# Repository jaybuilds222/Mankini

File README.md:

A custom mechanical keyboard design based on FlatFootFox's take on a single-board version of Brian Low's Sofle Choc keyboard, which is itself a redesigned version of the Sofle keyboard by Josef Adamčík. It uses MrZealot's excellent Ergogen engine to layout the design.

I've made two versions so far. One is designed to use Kailh V1 Choc low-profile keyswitches. The other is designed for Cherry MX switches.

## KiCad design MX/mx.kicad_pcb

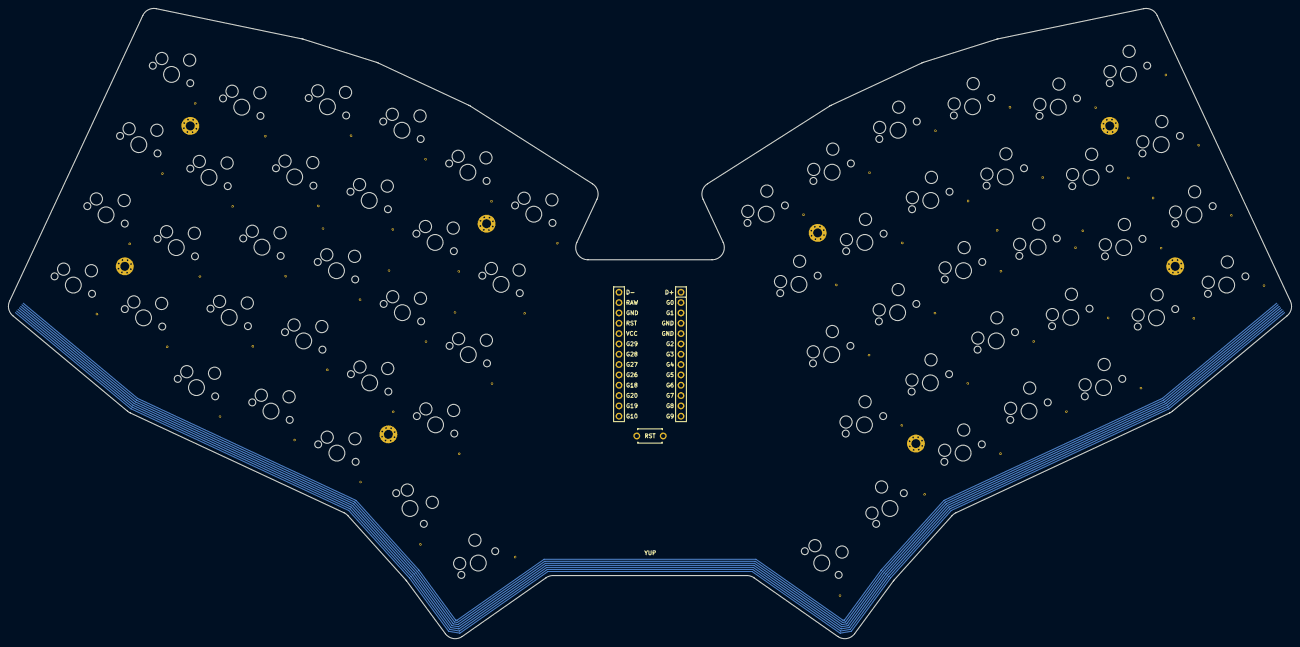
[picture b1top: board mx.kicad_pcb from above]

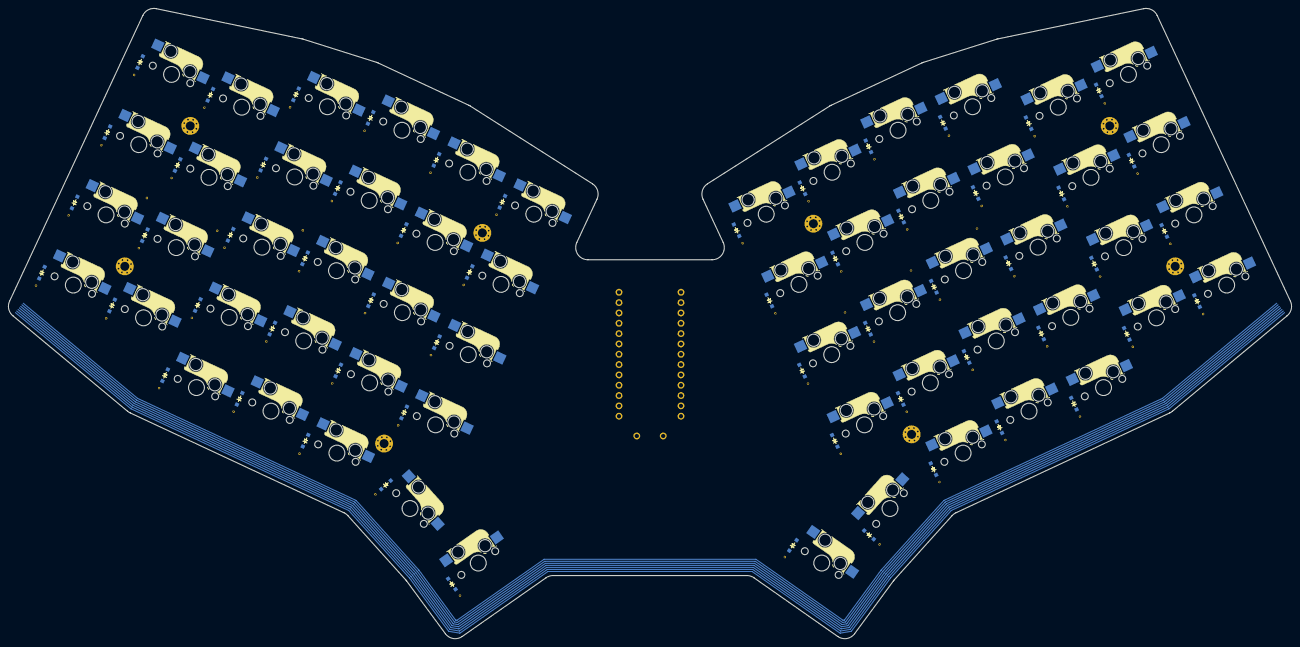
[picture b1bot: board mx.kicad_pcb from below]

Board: 2 copper layers, 315.5 x 155.0 mm, 126 parts (116 on the bottom side), 76 nets, no tracks yet.

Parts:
D1, D2, D3, D4, D5, D6, D7, D8, D9, D10, D11, D12, D13, D14, D15, D16, D17, D18, D19, D20, D21, D22, D23, D24, D25, D26, D27, D28, D29, D30, D31, D32, D33, D34, D35, D36, D37, D38, D39, D40, D41, D42, D43, D44, D45, D46, D47, D48, D49, D50, D51, D52, D53, D54, D55, D56, D57, D58: diode_tht_sod123
MCU1: mcu_rp2040
RST1: reset_switch_tht_top
S1, S2, S3, S4, S5, S6, S7, S8, S9, S10, S11, S12, S13, S14, S15, S16, S17, S18, S19, S20, S21, S22, S23, S24, S25, S26, S27, S28, S29, S30, S31, S32, S33, S34, S35, S36, S37, S38, S39, S40, S41, S42, S43, S44, S45, S46, S47, S48, S49, S50, S51, S52, S53, S54, S55, S56, S57, S58: switch_mx
_65, _66, _67, _68, _69, _70, _71, _72: MountingHole_2.2mm_M2_Pad_Via

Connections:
G2: D33.1, D37.1, D42.1, D47.1, D52.1, D56.1, MCU1.6
G3: D32.1, D36.1, D41.1, D46.1, D51.1, D55.1, MCU1.7
G4: MCU1.8, S1.1, S2.1, S3.1, S4.1, S30.1, S31.1, S32.1, S33.1
G5: MCU1.9, S5.1, S6.1, S7.1, S8.1, S9.1, S34.1, S35.1, S36.1, S37.1, S38.1
G6: MCU1.10, S10.1, S11.1, S12.1, S13.1, S14.1, S39.1, S40.1, S41.1, S42.1, S43.1
G7: D31.1, D35.1, D40.1, D45.1, D50.1, D54.1, MCU1.11
G8: D30.1, D34.1, D39.1, D44.1, D49.1, D53.1, MCU1.12
G9: D38.1, D43.1, D48.1, D57.1, D58.1, MCU1.13
G10: D9.1, D14.1, D19.1, D28.1, D29.1, MCU1.14
G18: MCU1.17, S24.1, S25.1, S26.1, S27.1, S29.1, S53.1, S54.1, S55.1, S56.1, S58.1
G19: D1.1, D5.1, D10.1, D15.1, D20.1, D24.1, MCU1.15
G20: D2.1, D6.1, D11.1, D16.1, D21.1, D25.1, MCU1.16
G26: MCU1.18, S20.1, S21.1, S22.1, S23.1, S28.1, S49.1, S50.1, S51.1, S52.1, S57.1
G27: MCU1.19, S15.1, S16.1, S17.1, S18.1, S19.1, S44.1, S45.1, S46.1, S47.1, S48.1
G28: D3.1, D7.1, D12.1, D17.1, D22.1, D26.1, MCU1.20
G29: D4.1, D8.1, D13.1, D18.1, D23.1, D27.1, MCU1.21
GND: MCU1.4, MCU1.5, MCU1.24, RST1.2
RST: MCU1.23, RST1.1
index_bottom: D20.2, S20.2
index_home: D21.2, S21.2
index_mod: D19.2, S19.2
index_num: D23.2, S23.2
index_top: D22.2, S22.2
inner_bottom: D24.2, S24.2
inner_home: D25.2, S25.2
inner_num: D27.2, S27.2
inner_top: D26.2, S26.2
middle_bottom: D15.2, S15.2
middle_home: D16.2, S16.2
middle_mod: D14.2, S14.2
middle_num: D18.2, S18.2
middle_top: D17.2, S17.2
mirror_index_bottom: D49.2, S49.2
mirror_index_home: D50.2, S50.2
mirror_index_mod: D48.2, S48.2
mirror_index_num: D52.2, S52.2
mirror_index_top: D51.2, S51.2
mirror_inner_bottom: D53.2, S53.2
mirror_inner_home: D54.2, S54.2
mirror_inner_num: D56.2, S56.2
mirror_inner_top: D55.2, S55.2
mirror_middle_bottom: D44.2, S44.2
mirror_middle_home: D45.2, S45.2
mirror_middle_mod: D43.2, S43.2
mirror_middle_num: D47.2, S47.2
mirror_middle_top: D46.2, S46.2
mirror_outer_bottom: D30.2, S30.2
mirror_outer_home: D31.2, S31.2
mirror_outer_num: D33.2, S33.2
mirror_outer_top: D32.2, S32.2
mirror_pinky_bottom: D34.2, S34.2
mirror_pinky_home: D35.2, S35.2
mirror_pinky_num: D37.2, S37.2
mirror_pinky_top: D36.2, S36.2
mirror_ring_bottom: D39.2, S39.2
mirror_ring_home: D40.2, S40.2
mirror_ring_mod: D38.2, S38.2
mirror_ring_num: D42.2, S42.2
mirror_ring_top: D41.2, S41.2
mirror_select_fan: D57.2, S57.2
mirror_space_fan: D58.2, S58.2
outer_bottom: D1.2, S1.2
outer_home: D2.2, S2.2
outer_num: D4.2, S4.2
outer_top: D3.2, S3.2
pinky_bottom: D5.2, S5.2
pinky_home: D6.2, S6.2
pinky_num: D8.2, S8.2
pinky_top: D7.2, S7.2
ring_bottom: D10.2, S10.2
ring_home: D11.2, S11.2
ring_mod: D9.2, S9.2
ring_num: D13.2, S13.2
ring_top: D12.2, S12.2
select_fan: D28.2, S28.2
space_fan: D29.2, S29.2
